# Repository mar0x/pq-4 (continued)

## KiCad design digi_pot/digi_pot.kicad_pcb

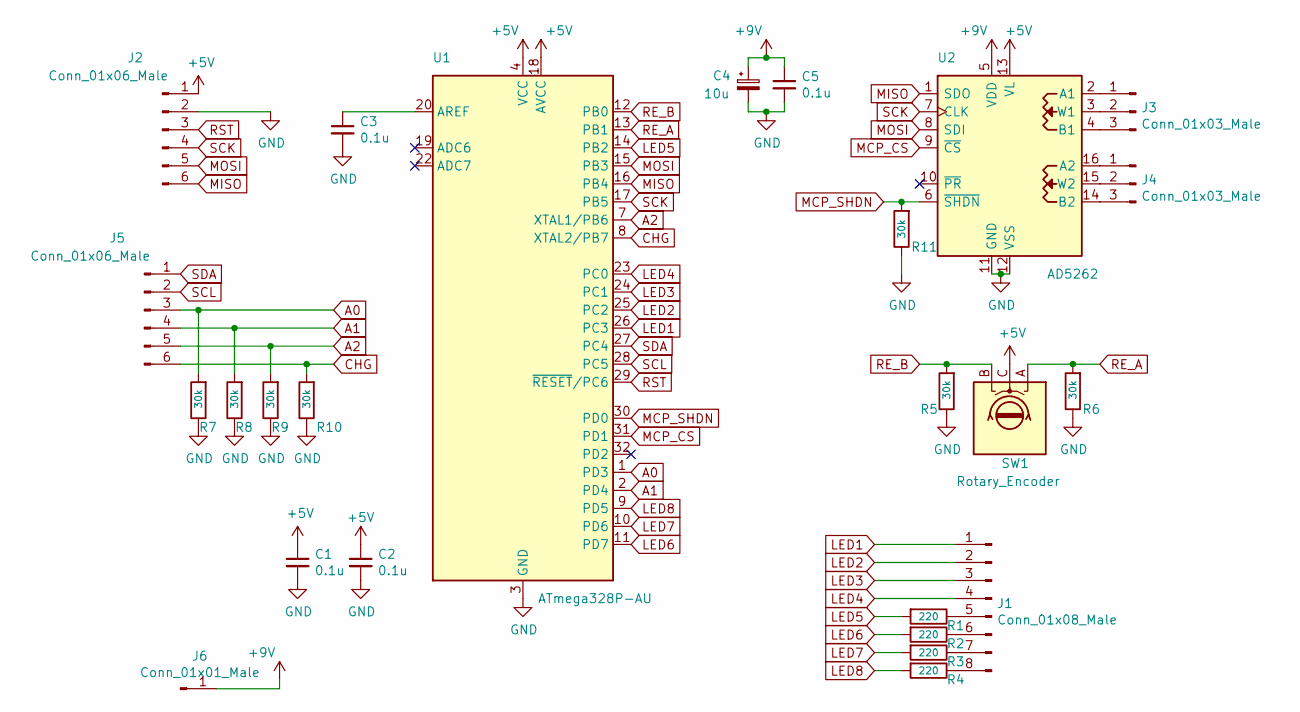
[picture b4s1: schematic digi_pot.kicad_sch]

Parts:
C1, C2, C3, C5: 0.1u; C_0805_2012Metric_Pad1.15x1.40mm_HandSolder
C4: 10u; CP_EIA-3216-18_Kemet-A_Pad1.58x1.35mm_HandSolder
J1: Conn_01x08_Male; Annular_LED_Ring
J2, J5: Conn_01x06_Male; PinHeader_1x06_P2.54mm_Vertical
J3, J4: Conn_01x03_Male; PinHeader_1x03_P2.54mm_Vertical
J6: Conn_01x01_Male; PinHeader_1x01_P2.54mm_Vertical
R1, R2, R3, R4: 220; R_0805_2012Metric_Pad1.15x1.40mm_HandSolder
R5, R6, R7, R8, R9, R10, R11: 30k; R_0805_2012Metric_Pad1.15x1.40mm_HandSolder
SW1: Rotary_Encoder; RotaryEncoder_Alps_EC12E_Vertical_H20mm
U1: ATmega328P-AU; TQFP-32_7x7mm_P0.8mm
U2: AD5262; TSSOP-16_4.4x5mm_P0.65mm

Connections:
+5V: C1.1, C2.1, J2.1, SW1.C, U1.4 (VCC), U1.6 (VCC), U1.18 (AVCC), U2.13 (VL)
+9V: C4.1, C5.1, J6.1, U2.5 (VDD)
A0: J5.3, R7.2, U1.1 (PD3)
A1: J5.4, R8.2, U1.2 (PD4)
A2: J5.5, R9.2, U1.7 (XTAL1/PB6)
CHG: J5.6, R10.2, U1.8 (XTAL2/PB7)
GND: C1.2, C2.2, C3.2, C4.2, C5.2, J2.2, R5.1, R6.1, R7.1, R8.1, R9.1, R10.1, R11.1, U1.3 (GND), U1.5 (GND), U1.21 (GND), U2.11 (GND), U2.12 (VSS)
LED1: J1.1, U1.26 (PC3)
LED2: J1.2, U1.25 (PC2)
LED3: J1.3, U1.24 (PC1)
LED4: J1.4, U1.23 (PC0)
LED5: R1.2, U1.14 (PB2)
LED6: R2.2, U1.11 (PD7)
LED7: R3.2, U1.10 (PD6)
LED8: R4.2, U1.9 (PD5)
MCP_CS: U1.31 (PD1), U2.9 (~CS)
MCP_SHDN: R11.2, U1.30 (PD0), U2.6 (~SHDN)
MISO: J2.6, U1.16 (PB4), U2.1 (SDO)
MOSI: J2.5, U1.15 (PB3), U2.8 (SDI)
unnamed: C3.1, U1.20 (AREF)
unnamed: J1.5, R1.1
unnamed: J1.6, R2.1
unnamed: J1.7, R3.1
unnamed: J1.8, R4.1
unnamed: J3.1, U2.2 (A1)
unnamed: J3.2, U2.3 (W1)
unnamed: J3.3, U2.4 (B1)
unnamed: J4.1, U2.16 (A2)
unnamed: J4.2, U2.15 (W2)
unnamed: J4.3, U2.14 (B2)
RE_A: R6.2, SW1.A, U1.13 (PB1)
RE_B: R5.2, SW1.B, U1.12 (PB0)
RST: J2.3, U1.29 (~RESET/PC6)
SCK: J2.4, U1.17 (PB5), U2.7 (CLK)
SCL: J5.2, U1.28 (PC5)
SDA: J5.1, U1.27 (PC4)

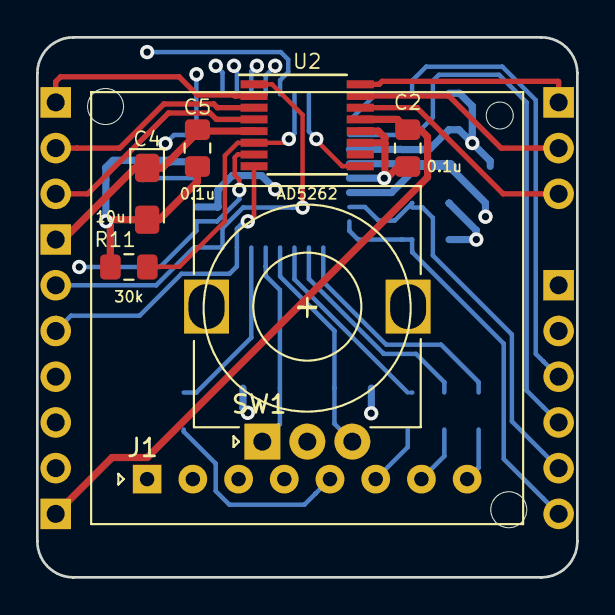
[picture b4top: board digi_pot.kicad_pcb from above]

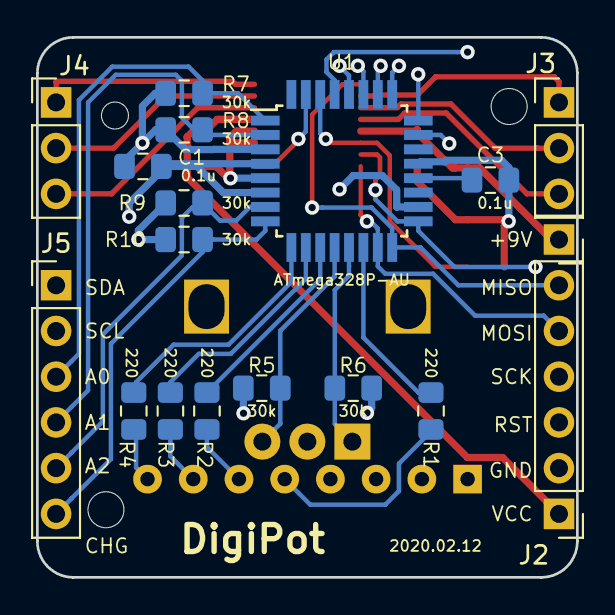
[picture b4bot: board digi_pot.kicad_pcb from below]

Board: 4 copper layers, 30.0 x 30.0 mm, 25 parts (18 on the bottom side), 36 nets.

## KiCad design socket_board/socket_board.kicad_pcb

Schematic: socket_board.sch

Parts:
J1: Barrel_Jack_Switch; BarrelJack_Wuerth_6941xx301002
J2, J3: DIN-5_180degree; DIN5MIDI-OOTDTY
J4, J5: AudioJack3; phone-jack-6.3
J6, J9: Conn_01x02_Male; JST_EH_B02B-EH-A_1x02_P2.50mm_Vertical
J7: Conn_01x03_Male; JST_EH_B03B-EH-A_1x03_P2.50mm_Vertical
J8: Conn_01x05_Male; JST_EH_B05B-EH-A_1x05_P2.50mm_Vertical
JP1: Jumper_3_Bridged12; PinHeader_1x03_P2.54mm_Vertical
K1: G6K-2; Relay_DPDT_Omron_G6K-2F-Y

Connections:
GND: J4.S, J5.S, J7.2
IN_T: J4.T, J7.3, K1.2
MIN_4: J2.4, J8.4
MIN_5: J2.5, J8.5
MOUT_2: J3.2, J8.2
MOUT_4: J3.4, J8.1
MOUT_5: J3.5, J8.3
unnamed: J5.T, JP1.2
unnamed: JP1.1, K1.3
OUT_T: J7.1, JP1.3, K1.4
POW1: J1.1, J6.1
POW2: J1.2, J6.2
REL+: J9.1, K1.1
REL-: J9.2, K1.8

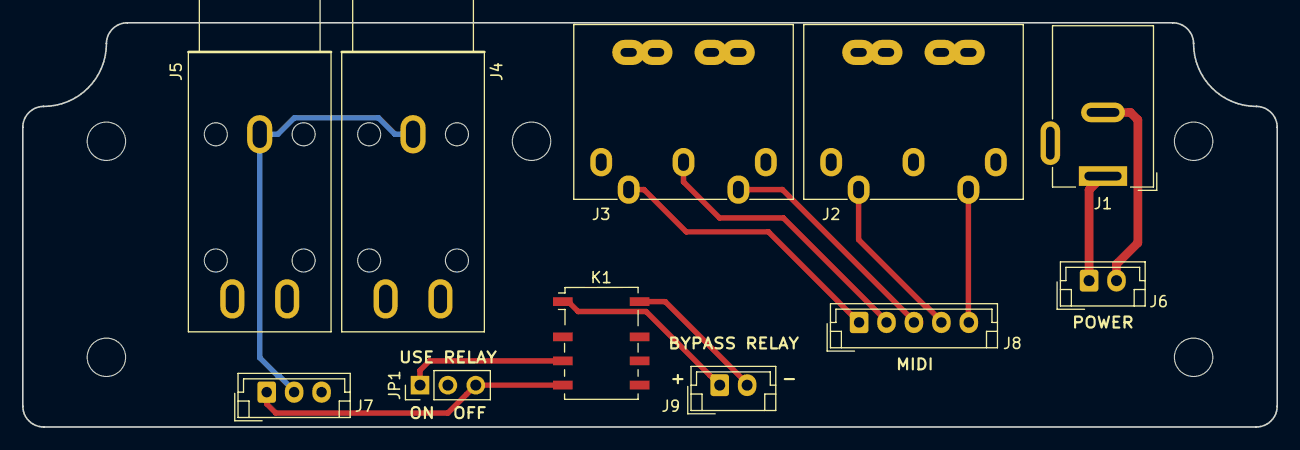
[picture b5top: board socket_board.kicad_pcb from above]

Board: 2 copper layers, 114.3 x 36.8 mm, 11 parts (0 on the bottom side), 14 nets.

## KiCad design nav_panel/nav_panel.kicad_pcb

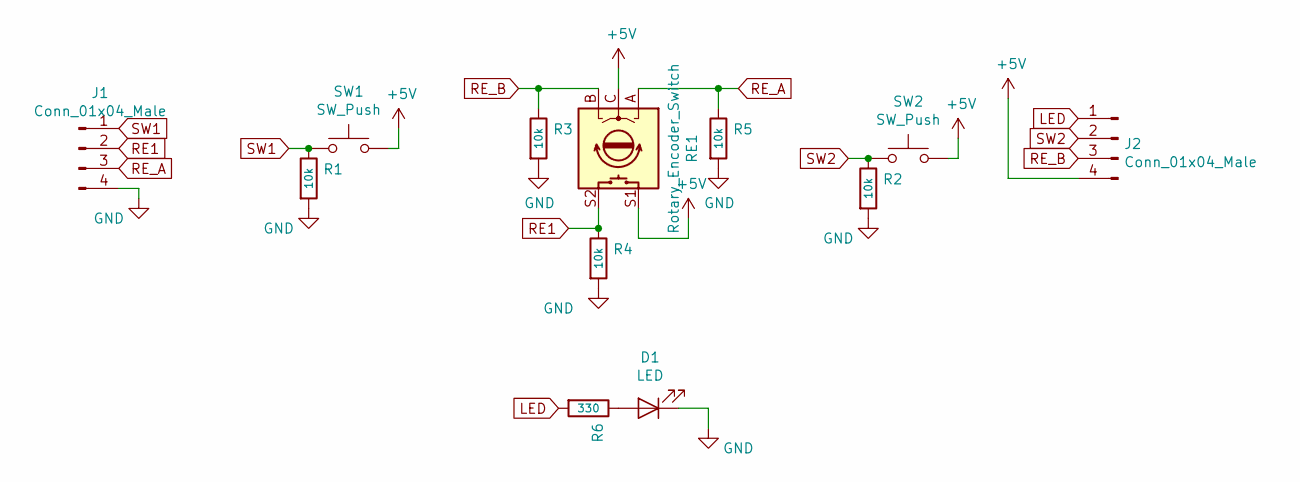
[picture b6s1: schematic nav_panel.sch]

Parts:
D1: LED; LED_D5.0mm
J1, J2: Conn_01x04_Male; PinHeader_1x04_P2.54mm_Vertical
R1, R2, R3, R4, R5: 10k; R_0805_2012Metric_Pad1.15x1.40mm_HandSolder
R6: 330; R_0805_2012Metric_Pad1.15x1.40mm_HandSolder
RE1: Rotary_Encoder_Switch; RotaryEncoder_Alps_EC12E-Switch_Vertical_H20mm
SW1, SW2: SW_Push; SW_PUSH_6mm_H5mm

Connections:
+5V: J2.4, RE1.C, RE1.S1, SW1.2, SW2.2
GND: D1.1 (K), J1.4, R1.2, R2.2, R3.2, R4.2, R5.2
LED: J2.1, R6.2
unnamed: D1.2 (A), R6.1
RE1: J1.2, R4.1, RE1.S2
RE_A: J1.3, R5.1, RE1.A
RE_B: J2.3, R3.1, RE1.B
SW1: J1.1, R1.1, SW1.1
SW2: J2.2, R2.1, SW2.1

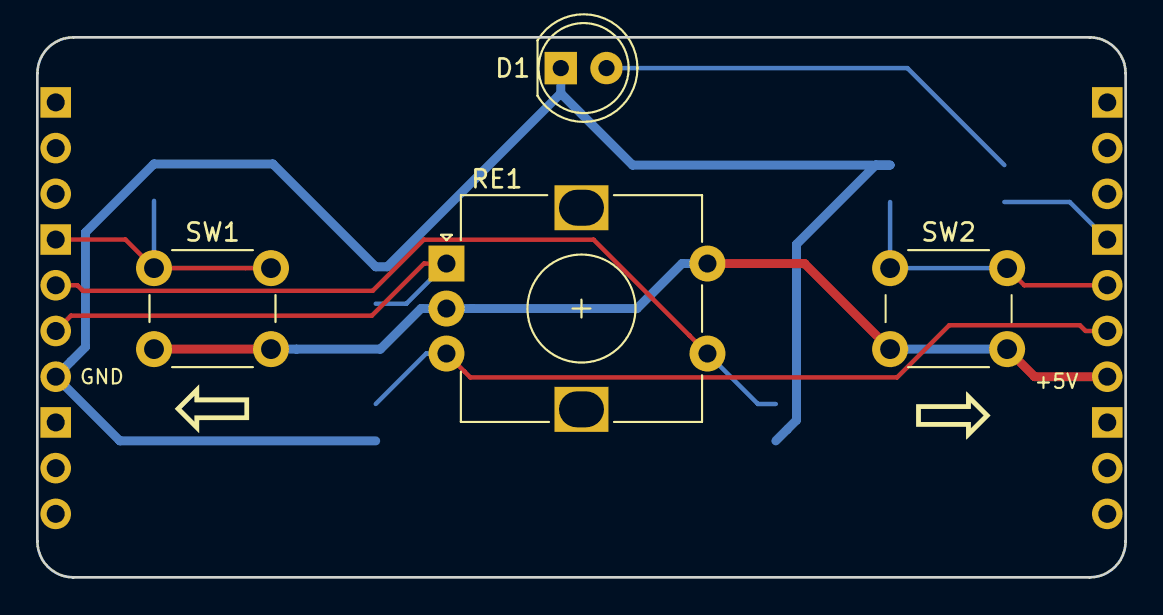
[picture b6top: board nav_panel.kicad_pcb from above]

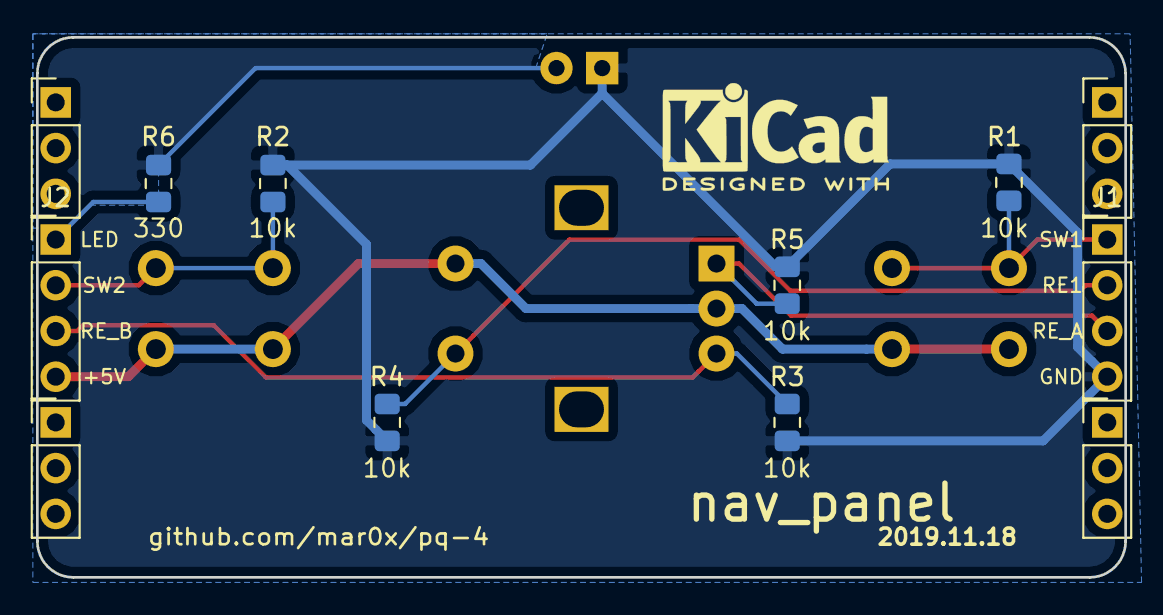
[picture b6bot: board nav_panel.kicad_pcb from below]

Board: 2 copper layers, 60.5 x 30.0 mm, 12 parts (8 on the bottom side), 9 nets.

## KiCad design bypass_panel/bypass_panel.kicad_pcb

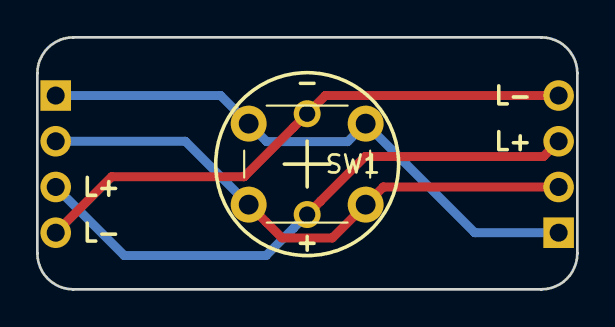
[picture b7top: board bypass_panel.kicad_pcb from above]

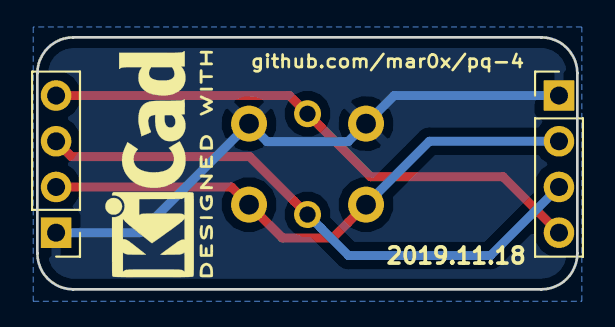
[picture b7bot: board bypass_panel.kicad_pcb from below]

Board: 2 copper layers, 30.0 x 14.0 mm, 3 parts (2 on the bottom side), 4 nets.

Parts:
J1, J2: Conn_01x04_Male; PinHeader_1x04_P2.54mm_Vertical
SW1: SW_MEC_5G_LED; SW_PUSH_6mm

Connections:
B1: J1.1, J2.1, SW1.1
B2: J1.2, J2.2, SW1.4
L+: J1.3, J2.3, SW1.3
L-: J1.4, J2.4, SW1.2

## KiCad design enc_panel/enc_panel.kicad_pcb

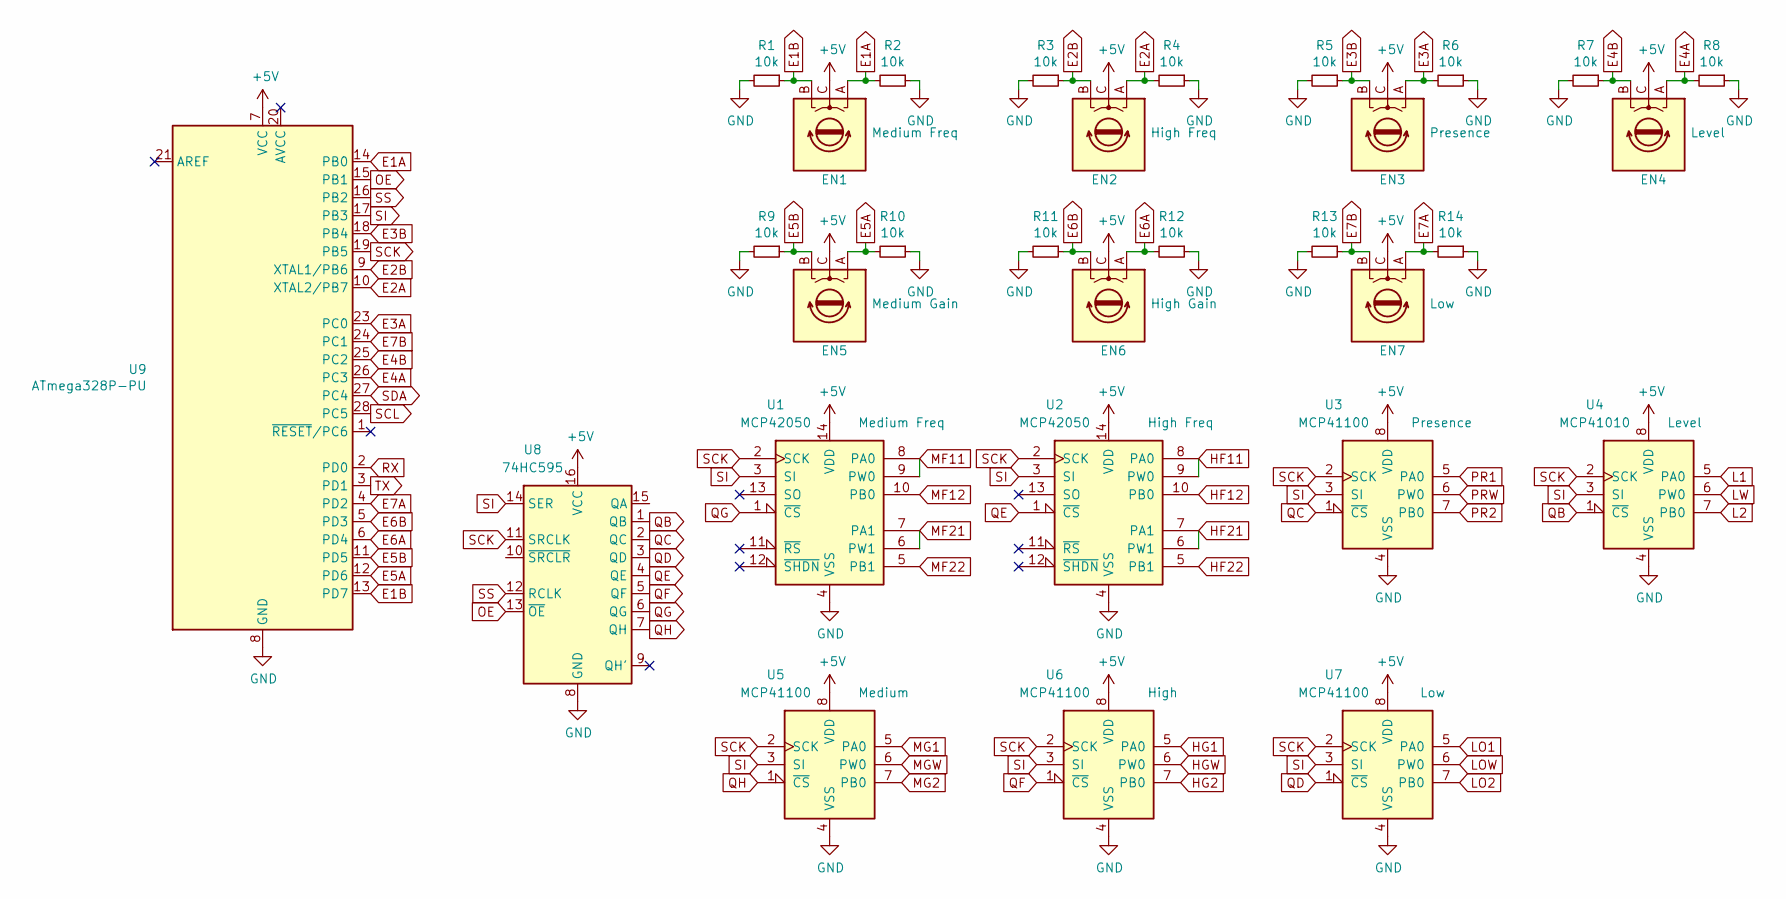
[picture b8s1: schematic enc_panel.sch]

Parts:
EN1: Medium Freq; RotaryEncoder_Alps_EC12E_Vertical_H20mm
EN2: High Freq; RotaryEncoder_Alps_EC12E_Vertical_H20mm
EN3: Presence; RotaryEncoder_Alps_EC12E_Vertical_H20mm
EN4: Level; RotaryEncoder_Alps_EC12E_Vertical_H20mm
EN5: Medium Gain; RotaryEncoder_Alps_EC12E_Vertical_H20mm
EN6: High Gain; RotaryEncoder_Alps_EC12E_Vertical_H20mm
EN7: Low; RotaryEncoder_Alps_EC12E_Vertical_H20mm
R1, R2, R3, R4, R5, R6, R7, R8, R9, R10, R11, R12, R13, R14: 10k; R_0805_2012Metric_Pad1.15x1.40mm_HandSolder
U1, U2: MCP42050; DIP-14_W7.62mm_Socket_LongPads
U3, U5, U6, U7: MCP41100; DIP-8_W7.62mm_Socket_LongPads
U4: MCP41010; DIP-8_W7.62mm_Socket_LongPads
U8: 74HC595; DIP-16_W7.62mm_Socket_LongPads
U9: ATmega328P-PU; DIP-28_W7.62mm_Socket_LongPads

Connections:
+5V: EN1.C, EN2.C, EN3.C, EN4.C, EN5.C, EN6.C, EN7.C, U1.14 (VDD), U2.14 (VDD), U3.8 (VDD), U4.8 (VDD), U5.8 (VDD), U6.8 (VDD), U7.8 (VDD), U8.16 (VCC), U9.7 (VCC)
E1A: EN1.A, R2.2, U9.14 (PB0)
E1B: EN1.B, R1.1, U9.13 (PD7)
E2A: EN2.A, R4.2, U9.10 (XTAL2/PB7)
E2B: EN2.B, R3.1, U9.9 (XTAL1/PB6)
E3A: EN3.A, R6.2, U9.23 (PC0)
E3B: EN3.B, R5.1, U9.18 (PB4)
E4A: EN4.A, R8.2, U9.26 (PC3)
E4B: EN4.B, R7.1, U9.25 (PC2)
E5A: EN5.A, R10.2, U9.12 (PD6)
E5B: EN5.B, R9.1, U9.11 (PD5)
E6A: EN6.A, R12.2, U9.6 (PD4)
E6B: EN6.B, R11.1, U9.5 (PD3)
E7A: EN7.A, R14.2, U9.4 (PD2)
E7B: EN7.B, R13.1, U9.24 (PC1)
GND: R1.2, R2.1, R3.2, R4.1, R5.2, R6.1, R7.2, R8.1, R9.2, R10.1, R11.2, R12.1, R13.2, R14.1, U1.4 (VSS), U2.4 (VSS), U3.4 (VSS), U4.4 (VSS), U5.4 (VSS), U6.4 (VSS), U7.4 (VSS), U8.8 (GND), U9.8 (GND), U9.22 (GND)
HF11: U2.8 (PA0), U2.9 (PW0)
HF12: U2.10 (PB0)
HF21: U2.6 (PW1), U2.7 (PA1)
HF22: U2.5 (PB1)
HG1: U6.5 (PA0)
HG2: U6.7 (PB0)
HGW: U6.6 (PW0)
L1: U4.5 (PA0)
L2: U4.7 (PB0)
LO1: U7.5 (PA0)
LO2: U7.7 (PB0)
LOW: U7.6 (PW0)
LW: U4.6 (PW0)
MF11: U1.8 (PA0), U1.9 (PW0)
MF12: U1.10 (PB0)
MF21: U1.6 (PW1), U1.7 (PA1)
MF22: U1.5 (PB1)
MG1: U5.5 (PA0)
MG2: U5.7 (PB0)
MGW: U5.6 (PW0)
OE: U8.13 (~OE), U9.15 (PB1)
PR1: U3.5 (PA0)
PR2: U3.7 (PB0)
PRW: U3.6 (PW0)
QB: U4.1 (~CS), U8.1 (QB)
QC: U3.1 (~CS), U8.2 (QC)
QD: U7.1 (~CS), U8.3 (QD)
QE: U2.1 (~CS), U8.4 (QE)
QF: U6.1 (~CS), U8.5 (QF)
QG: U1.1 (~CS), U8.6 (QG)
QH: U5.1 (~CS), U8.7 (QH)
RX: U9.2 (PD0)
SCK: U1.2 (SCK), U2.2 (SCK), U3.2 (SCK), U4.2 (SCK), U5.2 (SCK), U6.2 (SCK), U7.2 (SCK), U8.11 (SRCLK), U9.19 (PB5)
SCL: U9.28 (PC5)
SDA: U9.27 (PC4)
SI: U1.3 (SI), U2.3 (SI), U3.3 (SI), U4.3 (SI), U5.3 (SI), U6.3 (SI), U7.3 (SI), U8.14 (SER), U9.17 (PB3)
SS: U8.12 (RCLK), U9.16 (PB2)
TX: U9.3 (PD1)

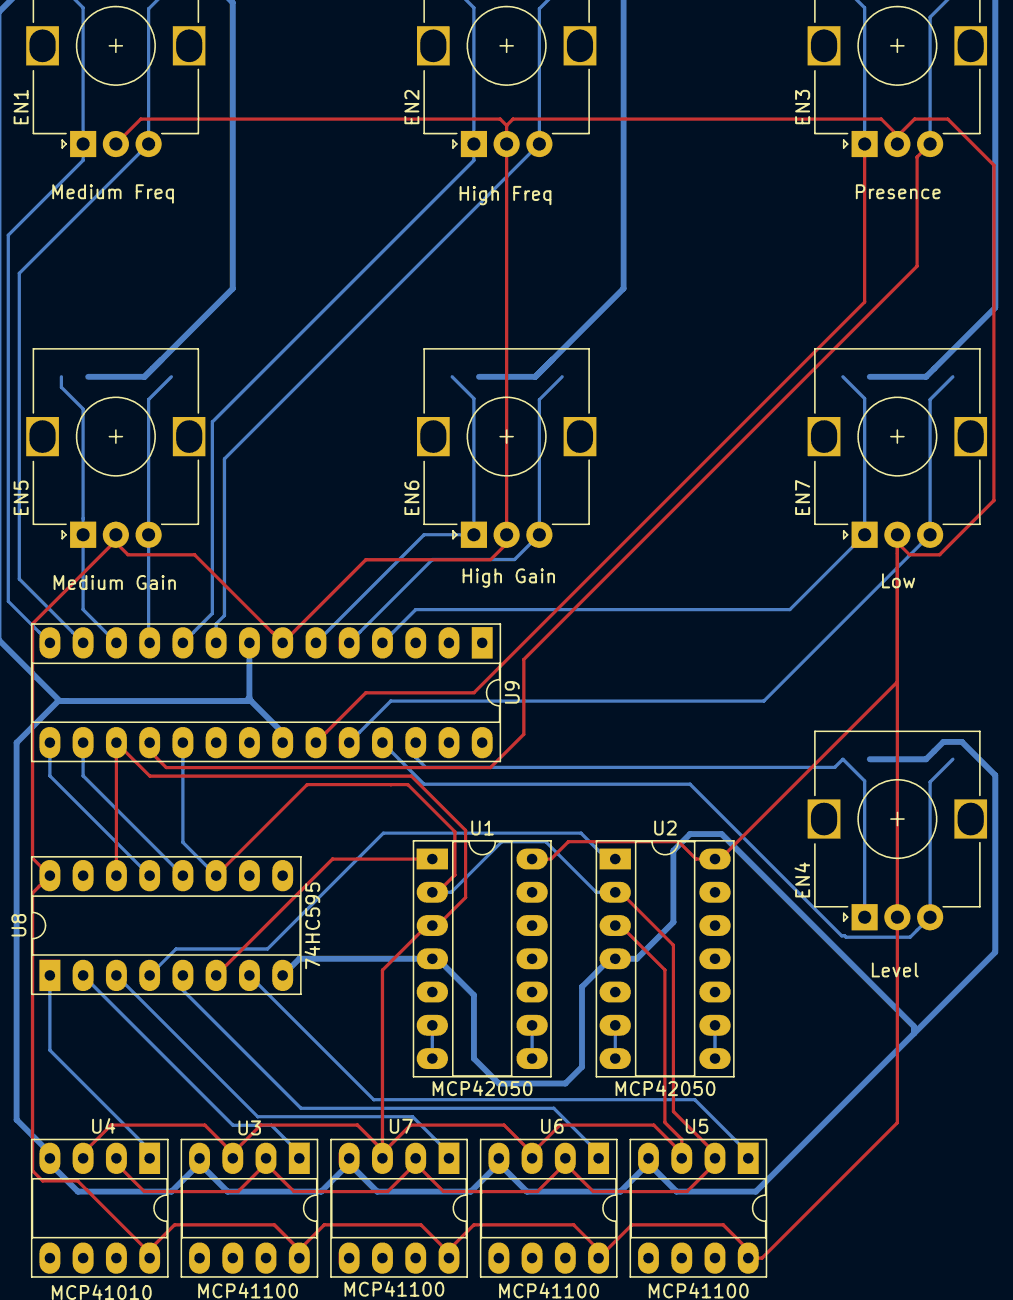
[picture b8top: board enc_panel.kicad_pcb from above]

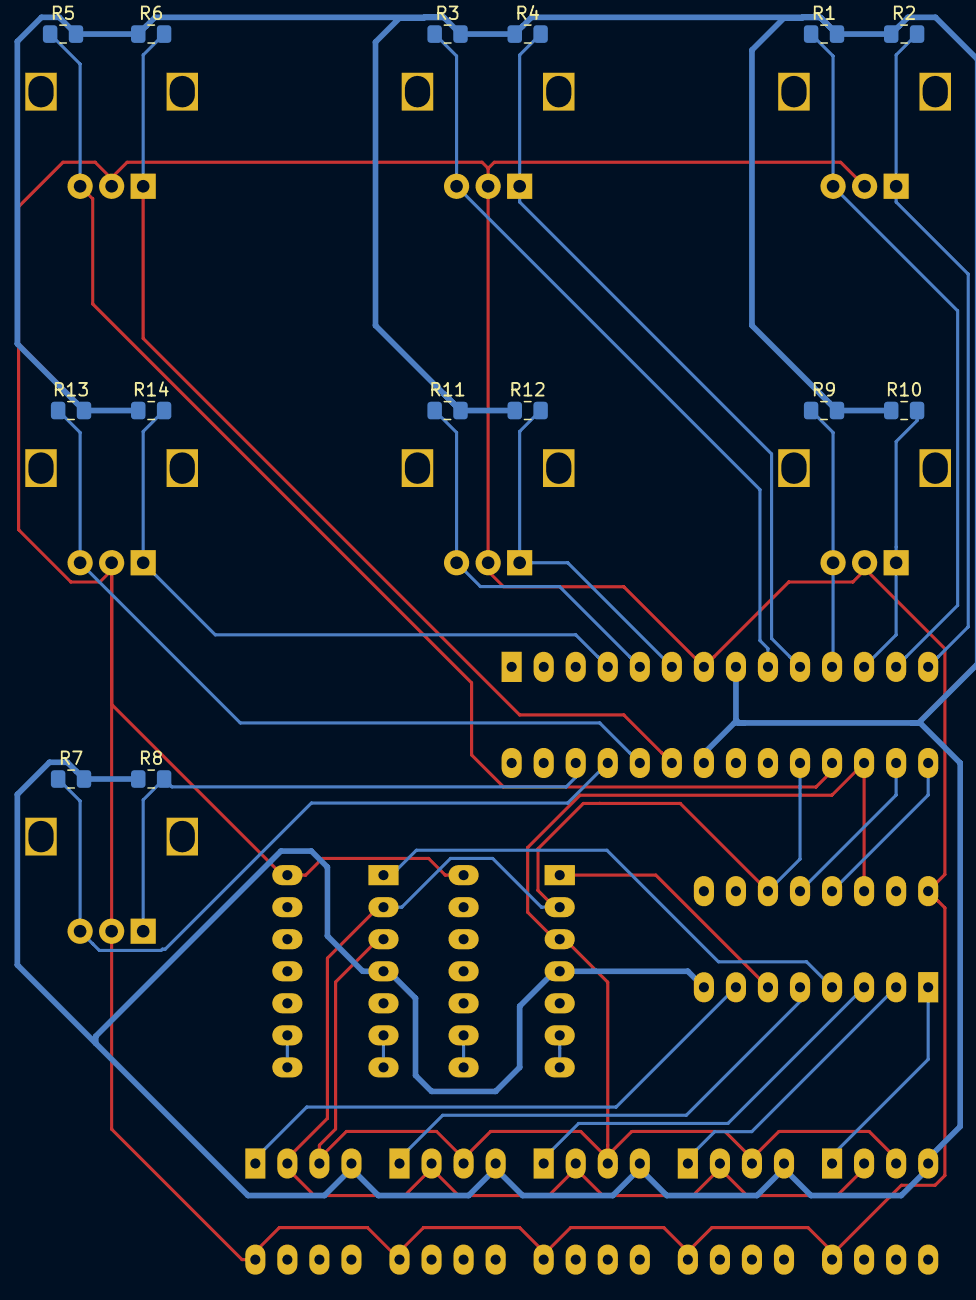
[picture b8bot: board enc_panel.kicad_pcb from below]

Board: 2 copper layers, 30 parts (14 on the bottom side), 31 nets.

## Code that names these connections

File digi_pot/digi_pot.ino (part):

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#include <SPI.h>
#include <Wire.h>

using re_a = artl::digital_in<artl::pin::id::pb1>;
using re_b = artl::digital_in<artl::pin::id::pb0>;

using re_a_change = artl::pin_change_int<re_a::pin>;
using re_b_change = artl::pin_change_int<re_b::pin>;

using a0 = artl::digital_in<artl::pin::id::pd3>;
using a1 = artl::digital_in<artl::pin::id::pd4>;
using a2 = artl::digital_in<artl::pin::id::pb6>;

using chg = artl::digital_pin<artl::pin::id::pb7>;

using led_update_tc = artl::tc<1>;

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        POS2LED_2 = POS2LED / 2,
    };

    using led1 = artl::digital_pin<artl::pin::id::pc3>;
    using led2 = artl::digital_pin<artl::pin::id::pc2>;
    using led3 = artl::digital_pin<artl::pin::id::pc1>;
    using led4 = artl::digital_pin<artl::pin::id::pc0>;
    using led5 = artl::digital_out<artl::pin::id::pb2>;
    using led6 = artl::digital_out<artl::pin::id::pd7>;
    using led7 = artl::digital_out<artl::pin::id::pd6>;
    using led8 = artl::digital_out<artl::pin::id::pd5>;

    void setup() {
        led1().input();
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led_array led_ring;

struct spi_pot {
    using cs = artl::digital_pin<artl::pin::id::pd1>;
    using shdn = artl::digital_pin<artl::pin::id::pd0>;

    void setup() {
        cs().output();
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
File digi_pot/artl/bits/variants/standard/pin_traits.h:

#pragma once

namespace artl {

namespace pin {
    namespace id {
        enum {
            pd0   = 0,
            rxd   = 0,
            rx    = 0,
            pd1   = 1,
            txd   = 1,
            tx    = 1,
            pd2   = 2,
            int0  = 2,
            pd3   = 3,
            int1  = 3,
            oc2b  = 3,
            pd4   = 4,
            t0    = 4,
            xck   = 4,
            pd5   = 5,
            t1    = 5,
            oc0b  = 5,
            pd6   = 6,
            ain0  = 6,
            oc0a  = 6,
            pd7   = 7,
            ain1  = 7,
            pb0   = 8,
            clko  = 8,
            icp1  = 8,
            pb1   = 9,
            oc1a  = 9,
            pb2   = 10,
            oc1b  = 10,
            ss_   = 10,
            pb3   = 11,
            oc2   = 11,
            mosi  = 11,
            pb4   = 12,
            miso  = 12,
            pb5   = 13,
            sck   = 13,

            pc0   = 14,
            a0    = 14,
            adc0  = 14,
            pc1   = 15,
            a1    = 15,
            adc1  = 15,
            pc2   = 16,
            a2    = 16,
            adc2  = 16,
            pc3   = 17,
            a3    = 17,
            adc3  = 17,
            pc4   = 18,
            a4    = 18,
            adc4  = 18,
            sda   = 18,
            pc5   = 19,
            a5    = 19,
            adc5  = 19,
            scl   = 19,

            micro_14 = 12,   mini_12 = micro_14,
            micro_15 = 13,   mini_13 = micro_15,
            micro_16 = 11,   mini_11 = micro_16,
            micro_18 = 14,   mini_14 = micro_18,
            micro_19 = 15,   mini_15 = micro_19,
            micro_20 = 16,   mini_16 = micro_20,
            micro_21 = 17,   mini_17 = micro_21,

            pb6 = 99,
            pb7 = 100,
        };
    }

    using oc0a = pin_traits<id::oc0a>;
    using oc0b = pin_traits<id::oc0b>;

    using oc1a = pin_traits<id::oc1a>;
    using oc1b = pin_traits<id::oc1b>;
};

template<>
struct pin_traits<0> : public base_pin_traits<port::D, 0> { };

template<>
struct pin_traits<1> : public base_pin_traits<port::D, 1> { };

template<>
struct pin_traits<2> : public base_pin_traits<port::D, 2> { };

template<>
struct pin_traits<3> : public base_pin_traits<port::D, 3> { };

template<>
struct pin_traits<4> : public base_pin_traits<port::D, 4> { };

template<>
struct pin_traits<5> : public base_pin_traits<port::D, 5> { };

template<>
struct pin_traits<6> : public base_pin_traits<port::D, 6> { };

template<>
struct pin_traits<7> : public base_pin_traits<port::D, 7> { };

template<>
struct pin_traits<8> : public base_pin_traits<port::B, 0> { };

template<>
struct pin_traits<9> : public base_pin_traits<port::B, 1> { };

template<>
struct pin_traits<10> : public base_pin_traits<port::B, 2> { };

template<>
struct pin_traits<11> : public base_pin_traits<port::B, 3> { };

template<>
struct pin_traits<12> : public base_pin_traits<port::B, 4> { };

template<>
struct pin_traits<13> : public base_pin_traits<port::B, 5> { };

template<>
struct pin_traits<14> : public base_pin_traits<port::C, 0> { };

template<>
struct pin_traits<15> : public base_pin_traits<port::C, 1> { };

template<>
struct pin_traits<16> : public base_pin_traits<port::C, 2> { };

template<>
struct pin_traits<17> : public base_pin_traits<port::C, 3> { };

template<>
struct pin_traits<18> : public base_pin_traits<port::C, 4> { };

template<>
struct pin_traits<19> : public base_pin_traits<port::C, 5> { };

template<>
struct pin_traits<pin::id::pb6> : public base_pin_traits<port::B, 6> { };

template<>
struct pin_traits<pin::id::pb7> : public base_pin_traits<port::B, 7> { };

}

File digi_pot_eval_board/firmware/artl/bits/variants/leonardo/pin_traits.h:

#pragma once

namespace artl {

namespace pin {
    namespace id {
        enum {
            pd2   = 0,
            rxd1  = 0,
            pd3   = 1,
            pd1   = 2,
            sda   = 2,
            pd0   = 3,
            oc0b  = 3,
            scl   = 3,
            pd4   = 4,
            a6    = 4,
            pc6   = 5,
            oc3a  = 5,
            oc4a_ = 5,
            pd7   = 6,
            a7    = 6,
            oc4d  = 6,
            pe6   = 7,
            pb4   = 8,
            a8    = 8,
            pb5   = 9,
            a9    = 9,
            oc1a  = 9,
            adc12 = 9,
            oc4b_ = 9,
            pb6   = 10,
            a10   = 10,
            oc1b  = 10,
            adc13 = 10,
            oc4b  = 10,
            pb7   = 11,
            oc0a  = 11,
            oc1c  = 11,
            rts_  = 11,
            pd6   = 12,
            a11   = 12,
            oc4d_ = 12,
            adc9  = 12,
            t1    = 12,
            pc7   = 13,
            oc4a  = 13,
            icp3  = 13,
            clko  = 13,
            led   = 13,
/*
            pf7   = 14,
            a0    = 14,
            adc7  = 14,
            tdi   = 14,
            pf6   = 15,
            a1    = 15,
            adc6  = 15,
            tdo   = 15,
            pf5   = 16,
            a2    = 16,
            adc5  = 16,
            tms   = 16,
            pf4   = 17,
            a3    = 17,
            adc4  = 17,
            tck   = 17,
*/
            pf7   = 18,
            a0    = 18,
            pf6   = 19,
            a1    = 19,
            pf5   = 20,
            a2    = 20,
            pf4   = 21,
            a3    = 21,
            pf1   = 22,
            a4    = 22,
            pf0   = 23,
            a5    = 23,

            micro_14 = 14,   mini_12 = micro_14,
            micro_15 = 15,   mini_13 = micro_15,
            micro_16 = 16,   mini_11 = micro_16,
            micro_18 = 18,   mini_14 = micro_18,
            micro_19 = 19,   mini_15 = micro_19,
            micro_20 = 20,   mini_16 = micro_20,
            micro_21 = 21,   mini_17 = micro_21,

            pd5   = 30,
        };
    }

    using oc0a = pin_traits<id::oc0a>;
    using oc0b = pin_traits<id::oc0b>;

    using oc1a = pin_traits<id::oc1a>;
    using oc1b = pin_traits<id::oc1b>;

    using oc4a = pin_traits<id::oc4a>;
    using oc4b = pin_traits<id::oc4b>;
    using oc4d = pin_traits<id::oc4d>;
};

template<>
struct pin_traits<0> : public base_pin_traits<port::D, 2> { };

template<>
struct pin_traits<1> : public base_pin_traits<port::D, 3> { };

template<>
struct pin_traits<2> : public base_pin_traits<port::D, 1> { };

template<>
struct pin_traits<3> : public base_pin_traits<port::D, 0> { };

template<>
struct pin_traits<4> : public base_pin_traits<port::D, 4> { };

template<>
struct pin_traits<5> : public base_pin_traits<port::C, 6> { };

template<>
struct pin_traits<6> : public base_pin_traits<port::D, 7> { };

template<>
struct pin_traits<7> : public base_pin_traits<port::E, 6> { };

template<>
struct pin_traits<8> : public base_pin_traits<port::B, 4> { };

template<>
struct pin_traits<9> : public base_pin_traits<port::B, 5> { };

template<>
struct pin_traits<10> : public base_pin_traits<port::B, 6> { };

template<>
struct pin_traits<11> : public base_pin_traits<port::B, 7> { };

template<>
struct pin_traits<12> : public base_pin_traits<port::D, 6> { };

template<>
struct pin_traits<13> : public base_pin_traits<port::C, 7> { };

template<>
struct pin_traits<14> : public base_pin_traits<port::B, 3> { };

template<>
struct pin_traits<15> : public base_pin_traits<port::B, 1> { };

template<>
struct pin_traits<16> : public base_pin_traits<port::B, 2> { };

template<>
struct pin_traits<17> : public base_pin_traits<port::B, 0> { };

template<>
struct pin_traits<18> : public base_pin_traits<port::F, 7> { };

template<>
struct pin_traits<19> : public base_pin_traits<port::F, 6> { };

template<>
struct pin_traits<20> : public base_pin_traits<port::F, 5> { };

template<>
struct pin_traits<21> : public base_pin_traits<port::F, 4> { };

template<>
struct pin_traits<22> : public base_pin_traits<port::F, 1> { };

template<>
struct pin_traits<23> : public base_pin_traits<port::F, 0> { };

template<>
struct pin_traits<24> : public base_pin_traits<port::D, 4> { };

template<>
struct pin_traits<25> : public base_pin_traits<port::D, 7> { };

template<>
struct pin_traits<26> : public base_pin_traits<port::B, 4> { };

template<>
struct pin_traits<27> : public base_pin_traits<port::B, 5> { };

template<>
struct pin_traits<28> : public base_pin_traits<port::B, 6> { };

template<>
struct pin_traits<29> : public base_pin_traits<port::D, 6> { };

template<>
struct pin_traits<30> : public base_pin_traits<port::D, 5> { };

}

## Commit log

2019-08-10 Initial commit.
2019-09-11 Minor improvements.
2019-09-23 Updating schema layout.
2019-09-23 Introducing DigiPot mini-board.
2019-10-09 External panels added
2019-10-09 Moving libraries to lib
2019-10-09 Removing generated files out of version control
2019-10-16 Added pin definition for PB6 & PB7.
    Usually this pins used for external crystal and not used in Arduino.
2019-10-16 Fixing A2 pin definition.
2019-10-16 Introducing 3D model for Annular LED Ring.
2019-10-16 Ignoring __pycache__.
2019-10-16 Adding draft encoder 3D model.
2019-10-16 Using 3D models for Annular LED Ring and encoder.
2019-10-16 Fixing MIDI optocoupler protection diode footprint.
2019-10-18 Disabling 'shutdown' pot state.
2019-10-18 Shutdown pull down resistor labels aligned.
2019-10-27 Pointless refactoring.
2019-10-27 EC12E encoder 3D model added.
2019-10-27 Wide nav_panel version.
2019-10-27 DIN-5 MIDI female connector 3D model draft added.
2019-10-27 Jack 6.3mm footprint added.
2019-10-27 Before wide nav_panel and Level pot move.
2019-10-27 Introducing socket board.
2019-10-31 Navigation panel wide version.
2019-10-31 Added OLED 1602 module footprint.
2019-10-31 Introducing BOM text file.
2019-10-31 Adjusting socket board dimensions.
2019-10-31 Introducing new layout.
2019-10-31 Moving original PQ-4 photos to img/pq-4.
2019-10-31 Adding various images.
2019-11-13 Introducing bypass panel with LED button.
2019-11-13 Printed and tested layout version.
    USB still on upper board.
2019-11-18 Removing gerber files from source control.
2019-11-18 Production version 2019.11.19.
2019-12-05 Reverting Annular LED low profile to original height.
2019-12-05 Generating short pin headers for low profile boards.
2019-12-05 Generating DigiPot 3D model.
2019-12-06 Adding 3D models.
2019-12-06 Adding case 3D models.
2019-12-06 Adding board 3D model.
2019-12-25 Adding datasheets.
2019-12-25 Adding I2C communication.
2019-12-25 Adding more components.
2019-12-25 Updating box model.
2020-01-16 Diode bridge added.
2020-01-16 Introducing I2C registers.
2020-01-16 Upgrading KiCad and fixing ULN2003a connection.
2020-01-16 Firmware alpha version.
2020-02-12 Changing pos <-> SPI command mapping.
    Highlight renamed to Red dot.
2020-02-12 Switching to AD5262 digital pot.
2020-02-12 Moving Annular LED holes by 0.2mm out.
2020-02-12 Using standard Atmega328 symbol.
2024-01-06 Switch to 8-bit pot value
2024-01-06 Add AD5262 symbol library
2024-01-06 Serial interface improvements
2024-01-06 Phone Jack fix
2024-01-06 Minor schematic changes
2024-01-06 Updating BOM
2024-01-06 digi_pot: switch to KiCad 7.0
2024-01-06 digi_pot_eval_board: switch to KiCad 7.0
2024-01-06 pq-4: switch to KiCad 7.0
2024-01-06 Updated schematic
2024-01-06 AD5262 datasheet added
2024-01-09 Introducing POT board
2024-01-14 Working on POT Board
